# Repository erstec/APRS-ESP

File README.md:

# APRS-ESP32 Project — v2.1

APRS-ESP32 is an APRS AFSK1200 Tracker + Digipeater + Internet Gateway for Espressif ESP32/ESP32-S3 MCUs.

> **v2.0 breaking change:** filesystem migrated from SPIFFS to LittleFS. All web UI assets are stored on LittleFS. A full flash (firmware + filesystem) is required when upgrading from v1.x.

Feel free to ask [Me](https://github.com/erstec) by creating a [Discussion](https://github.com/erstec/APRS-ESP/discussions/new), by e-mail.

---

## Features

### Firmware

- IGate (APRS-IS internet gateway)
- Digipeater
- Tracker with SmartBeaconing
- Fixed position and item beaconing
- APRS message receive: inbox with unread counter, popup notification, and automatic ACK
- Received APRS packet list with raw packet viewer
- OLED display with rotary encoder menu, live GNSS status screen, and graphical APRS symbol picker
- Automatic GNSS configuration on boot: GPS+BeiDou+GLONASS, NMEA output filtered to GGA/GSA/RMC (T-TWR Plus / Quectel L76K)
- Web interface for all configuration
- Interactive map location picker with GPS fix-from-device button; offline tiles bundled for use without internet
- Graphical APRS symbol picker in web UI and OLED menu
- Visual APRS-IS filter builder (range, prefix, buddy, type tokens)
- Battery / PMU status dashboard card (charger state, voltage, %, VBUS, sys voltage, PMU temperature)
- Configuration backup / restore (JSON)
- OTA firmware update via web interface

### Supported Hardware

| Target | Notes |
| ------ | ----- |
| **LilyGO T-TWR Plus (Rev 2.0)** | Fully supported, recommended |
| **LilyGO T-TWR V1** | Supported (UNTESTED) with hardware mods — see [doc/mod-hw-devel.md](doc/mod-hw-devel.md) |
| **ESP32-DevKitC + SA818/SA868** | DIY build — see schematics below |

> **esp32dev-t-twr-mod is removed** — that variant was an intermediate hardware mod that is no longer maintained.

---

## OLED Display

### Main status screen

The display is 128×64 pixels. The speed/heading zone uses a large proportional font; all other zones use the default 6×8 bitmap font. `[sat]` `[clk]` `[->]` represent 8×7 px graphical bitmap icons.

```text
N0CALL-9              A+ [wifi][bat]  <- callsign / APRS-IS / WiFi / battery
                                      | large font zone
  45 km/h                    265°     <- speed (left) · heading (right)
                                      |
N0000.00  W00000.00                   <- coordinates (NMEA)
AA00aa    12:34:56           0m       <- locator / time / altitude
[sat]8++GPS        SB TN IS RI       <- satellites / sync source / flags
[clk]42s   AUTO      [->]1234        <- GPS age / send mode / distance
```

| Zone | Position | Content | Values / meaning |
| ---- | -------- | ------- | ---------------- |
| Callsign | left | **Callsign + SSID** | `{MYCALL}-{SSID}` |
| Callsign | right | **APRS-IS status** | `A+` connected, `A-` disconnected (only when APRS-IS enabled) |
| Callsign | right | **WiFi icon** | Rising signal bars = connected to AP; X + bar = disconnected (only when WiFi enabled) |
| Callsign | right | **Battery icon** | Outline + proportional fill; lightning bolt when charging |
| Speed/Heading | left | **Speed** | Ground speed in km/h (large font); `Waiting for FIX` / `NO GNSS` when no satellites |
| Speed/Heading | right | **Heading** | Course in degrees + ° (large font); hidden when no satellites |
| Coordinates | full | **Lat + Lon** | NMEA format `NDDMM.MM WDDDMM.MM`; zeroed when no fix |
| Locator row | left | **QTH locator** | Maidenhead grid square (6-char); `------` when no GPS fix |
| Locator row | center | **Time** | `HH:MM:SS` local time; `NO TIME` if not yet synced |
| Locator row | right | **Altitude** | Metres above sea level; blank when no fix |
| Satellites | left | **[sat icon] Satellite info** | `{count}{fix}{pkt}` — count; `+`/`-` for valid fix; `+`/`-` for GPS packets received |
| Satellites | left | **Time sync source** | `GPS`, `NTP`, `APR` = source; `NO` = not synced |
| Satellites | right | **Beacon mode + flags** | `SB` SmartBeaconing, `T{n}` = fixed interval (min); `TN` RF, `TM` telemetry, `DG` digi, `IS` APRS-IS, `RI` RF→IGate, `IR` IGate→RF |
| Bottom | left | **[clock icon] GPS age** | Seconds since last valid fix; `--s` when no fix |
| Bottom | center | **Send mode** | `AUTO` (GPS→Fixed fallback), `GPS` (GPS-only), `FIX` (fixed position) |
| Bottom | right | **[arrow icon] Distance** | Distance travelled since last beacon; `0` when no fix |

### Non-tracker screen (IGate / Digipeater / fixed-position mode)

When operating as an IGate, Digipeater, or fixed-position beacon (GPS mode = Fixed), the tracker speed/heading zone is replaced with a station monitor view.

```text
N0CALL-9              A+ [wifi][bat]  <- callsign / APRS-IS / WiFi / battery
                                      | large font zone
           N0CALL-1                   <- last-heard station callsign (centered)
                                      |
           RF 42s ago                 <- source (RF/IS) + age since last heard
RX:1234              DG:56            <- total packets received / digipeated
RI:78                IR:9             <- RF→IGate / IGate→RF counts
[sat]8++NTP                12:34:56  <- satellites / sync source / time
                    SB TN IS RI IR   <- beacon mode + active service flags
```

| Zone | Position | Content | Values / meaning |
| ---- | -------- | ------- | ---------------- |
| Callsign | left | **Callsign + SSID** | `{MYCALL}-{SSID}` |
| Callsign | right | **APRS-IS status** | `A+` connected, `A-` disconnected (only when APRS-IS enabled) |
| Callsign | right | **WiFi icon** | Rising bars = connected; X + bar = disconnected (only when WiFi enabled) |
| Callsign | right | **Battery icon** | Outline + proportional fill; lightning bolt when charging |
| Large zone | center | **Last-heard callsign** | Most recently decoded station (RF or APRS-IS); blank until first packet |
| Large zone | center | **Source + age** | `RF` or `IS` + time since last packet (`Xs ago`, `Xm ago`, `Xh ago`); `---` if none yet |
| Stats | left | **RX count** | Total packets received |
| Stats | right | **DG count** | Total packets digipeated |
| Stats | left | **RI count** | Packets gated RF → APRS-IS |
| Stats | right | **IR count** | Packets injected APRS-IS → RF |
| Satellites | left | **[sat icon] Satellite info** | `{count}{fix}{pkt}` — count; `+`/`-` for valid fix; `+`/`-` for GPS packets received |
| Satellites | left | **Time sync source** | `GPS`, `NTP`, `APR` = source; `NO` = not synced |
| Satellites | right | **Time** | `HH:MM:SS` local time |
| Flags | right | **Beacon mode + flags** | `SB` SmartBeaconing, `T{n}` = fixed interval (min); `TN` RF, `TM` telemetry, `DG` digi, `IS` APRS-IS, `RI` RF→IGate, `IR` IGate→RF |

---

## Rotary Encoder Menu

### Short press — enter main menu

Scroll with the encoder knob. Press to select / toggle each item:

| # | Item | Action |
| - | ---- | ------ |
| 0 | Send Beacon | Transmit position now |
| 1 | Beacon Mode | Select: SmartBeaconing (SB) or fixed interval 1/2/5/10/15/20/30/60 min |
| 2 | WiFi | Cycle: OFF → AP → STA → AP+STA |
| 3 | APRS-IS | Toggle ON/OFF |
| 4 | Digi | Toggle digipeater ON/OFF |
| 5 | RF/TNC | Toggle RF modem ON/OFF |
| 6 | RF Power | Toggle Low / High transmit power |
| 7 | Send Mode | Cycle: AUTO (GPS→Fixed fallback) / GPS only / Fixed position |
| 8 | Callsign-SSID | Edit callsign (A-Z, 0-9, min 3 chars, max 6) then SSID (0-15) |
| 9 | Symbol | Graphical APRS symbol picker: scroll through 12 presets (Car, House, Hiker, Bike, …), OLED shows the symbol bitmap + table/char code |
| 10 | Brightness | Set OLED brightness: Min / Low / Medium / High / Max |
| 11 | Auto-Dim | Set auto-dim timeout and level |
| 12 | Locator Popup | Duration of grid locator popup (OFF or 1–10 s) |
| 13 | APRS RX Popup | Duration of received packet popup (OFF or 1–10 s) |
| 14 | SMS Popup | Duration of incoming APRS message popup (OFF / 15 / 30 / 60 s); OFF falls back to transient RX popup |
| 15 | RX Packet List | Scrollable list of received APRS packets; press to view full raw packet |
| 16 | MSG Inbox | Received APRS messages; shows unread count |
| 17 | GNSS Status | Live GNSS data screen (see below) |
| 18 | Battery Status | Live battery / PMU status (charger state, voltage, %, VBUS, sys voltage, PMU temp) |
| 19 | About | Firmware version, callsign and IP address |
| 20 | Factory Reset | Erase all settings (YES/NO confirmation) |

Long press from inside the menu → exit without saving.

### GNSS Status screen (item 17)

Live GNSS data, updated every second. Press to return to menu.

```text
   GNSS STATUS
GPS:5  BDS:3  GLO:4
Lat: 5412.34N
Lon: 02512.34E
Alt: 123.4m  3D
Spd: 12.3  Crs: 180
HDOP:1.2 Sat:12 #17
press: back
```

| Row | Content |
| --- | ------- |
| 1 | Satellites **in use** per constellation: GPS / BDS (BeiDou) / GLO (GLONASS) |
| 2 | Latitude in NMEA format (DDMM.MMN/S); `--------` when no fix |
| 3 | Longitude in NMEA format (DDDMM.MME/W); `---------` when no fix |
| 4 | Altitude in metres + fix type (`3D` / `2D`); `---` when no fix |
| 5 | Ground speed (km/h) and course (degrees); `0` when no fix |
| 6 | HDOP value, total satellites in use, rolling packet counter (`#XX`) — visible even before a fix to confirm the module is alive and sending |

### Long press — quick action picker

Hold the button. A large message cycles through quick actions every 2 seconds:

| Shown | Action on release |
| ----- | ----------------- |
| **BEACON** | Send position packet |
| **WiFi SW** | Toggle WiFi ON/OFF (device restarts) |
| **RF SW** | Toggle RF modem ON/OFF |
| **SB SW** | Toggle SmartBeaconing ON/OFF |
| **RESET** | Factory reset (device restarts) |
| **Cancel** | Do nothing |

*Release when the desired action is shown.*

---

## BOOT Button (GPIO0, all boards)

The physical BOOT button on the ESP32 module provides the same timed quick actions on boards **without** a rotary encoder:

- Short press (< 5 s) → Send position
- Hold **5 s** → Toggle WiFi (shows "WiFi SW")
- Hold **10 s** → Toggle RF modem (shows "RF SW")
- Hold **15 s** → Toggle SmartBeaconing (shows "SB SW")
- Hold **20 s** → Factory reset (shows "Reset")
- Hold **25 s+** → Cancel

*Release when the desired message appears on screen.*

---

## Side Buttons (T-TWR Plus only)

The T-TWR Plus has three physical buttons in addition to the rotary encoder:

| Button | Short press | Long press (2 s) |
| ------ | ----------- | ---------------- |
| **Lower** | Toggle OLED display on/off; dismiss active popup | Toggle RF power High ↔ Low |
| **Middle** | Show battery status popup (voltage, %, charge state); dismiss active popup | — |
| **Upper** | Send beacon now | Toggle RF/TNC on/off |

> On boards **without** a rotary encoder, SW1/BOOT reverts to the timed BOOT button actions described above.

---

## Flashing Firmware

### First-time flash — new device or upgrade from v1.x

> **v2.0 note:** upgrading from v1.x requires a full flash (firmware + filesystem). The factory `.bin` contains everything — one file, one step.

#### Browser flasher — no software to install (recommended)

Works in **Chrome, Edge or Firefox** on any OS via the Web Serial API.

1. [Download](https://github.com/erstec/APRS-ESP/releases) the factory binary for your hardware, e.g. `firmware-lilygo-t-twr-plus-2.1.factory.bin`
2. Open **<https://espressif.github.io/esptool-js/>** in Chrome, Edge or Firefox
3. Click **Connect** — select the **ESP32-S3 native USB** port (listed as `USB JTAG/serial debug unit`, VID `303a`), not the CH340 UART port
4. Add one row: offset **`0x0`**, select the downloaded `.factory.bin` file
5. Click **Program** — erases flash and writes everything in one pass

#### Via USB script (Python + esptool)

```sh
# Linux / macOS
bin/device-install.sh -f firmware-lilygo-t-twr-plus-2.1.factory.bin

# Windows
bin\device-install.bat -f firmware-lilygo-t-twr-plus-2.1.factory.bin
```

Requires Python 3 and `pip install esptool`. The `-p PORT` flag is optional (esptool auto-detects).

#### From source (PlatformIO)

```bash
pio run -e lilygo-t-twr-plus -t upload
pio run -e lilygo-t-twr-plus -t uploadfs
```

---

## Updating Firmware

### Via web interface (easiest, no USB needed)

> **Before updating:** export your config (Storage tab → Download config). Restore it after flashing via the same tab if needed.

Go to the **Firmware** tab in the web UI:

- Upload `firmware-lilygo-t-twr-plus-2.1-update.bin` → flashes app only, config is preserved
- Upload `littlefs-lilygo-t-twr-plus-2.1.bin` → updates web assets (upload after firmware if web UI changed)

The page auto-detects which file type you selected by filename.

### Via browser flasher (upgrade from v1.x or broken web UI)

Same steps as first-time flash above — use the `.factory.bin` at offset `0x0`.

### Via USB script

```sh
bin/device-update.sh -f firmware-lilygo-t-twr-plus-2.1-update.bin
```

> After any major update: export a configuration backup first — config format changes between versions are not guaranteed.

---

## WiFi / Web Interface

On first boot the device creates a WiFi AP:

- **SSID**: `APRS-ESP32`
- **Password**: `aprs-esp32`
- **URL**: <http://192.168.4.1>

### Web UI tabs

| Tab | Contents |
| --- | -------- |
| **Dashboard** | System status (CPU temp, free heap, uptime, WiFi RSSI); **Battery Status** (charger state, voltage %, VBUS, sys voltage, PMU temp); GNSS status (fix, coords, altitude, speed, sats/HDOP, per-constellation counts); packet statistics; last heard stations; top senders |
| **Config** | APRS callsign, SSID, passcode, beacon interval / SmartBeaconing, digi path, symbol (graphical tile picker + manual table/char fields); **interactive Leaflet map** with draggable marker and "Use current GPS location" button (offline tiles bundled) |
| **Radio** | SA818/SA868: TX/RX frequency, bandwidth, RF power, squelch, volume; OLED brightness and auto-dim timeout |
| **Service** | APRS-IS enable/server/port/filter with **visual filter builder** (range, prefix, buddy, type tokens); TNC / RF→INET / INET→RF / telemetry / digipeater toggles; digi delay; TX time slot; BPF enable |
| **System** | Manual date/time set, NTP sync, timezone offset; WiFi AP and client config with live status (mode, IP, MAC, SSID, gateway, DNS); reboot |
| **Test** | Send beacon now; send raw TNC2 packet; live audio **VU meter**; APRS-IS terminal log |
| **Files** | LittleFS file browser — upload, download, delete; in-browser **CodeMirror editor** for web asset files (HTML, JS, CSS, JSON, config) |
| **Firmware** | OTA firmware update (`-update.bin`) and filesystem update (`littlefs-*.bin`) |
| **Configuration** | Device info (board, firmware version, chip ID); config **backup** (JSON download) and **restore** (JSON upload) |

---

## Serial Monitor (Development Tool)

`tools/monitor.py` is a live desktop monitor for development and field debugging. It reads the device serial port, parses structured JSON log lines, and displays them in real-time cards.

### Requirements

```sh
pip install -r tools/requirements.txt   # dearpygui, pyserial
```

### Usage

```sh
python3 tools/monitor.py
```

The best available ESP32 port is pre-selected on startup. Connect, disconnect, and optionally log to file via the toolbar.

### Cards

| Card | Content |
| ---- | ------- |
| **System** | Time, uptime, free heap, CPU temp, WiFi RSSI, IP address |
| **Config** | Callsign, path, beacon, send mode, RX/TX freq, mode flags, WiFi mode, routing, APRS-IS |
| **Battery** | Charge %, voltage, VBUS, system voltage, charger state, PMU temp |
| **GPS** | Fix, lat/lon, altitude, speed, heading, HDOP, sats (GPS/BDS/GLO), data age |
| **APRS** | Packet counters (all/drop/RF→IS/IS→RF) |
| **SmartBeaconing** | Distance, speed, elapsed, rate, turn angle, will-TX flag |
| **RF** | PTT state, last TX packet, last RX packet, last SMS addressed to this station |
| **Log** | Colour-coded raw serial log (STATUS / DEBUG / SB / TX / BTN / MSG / PKT); toggleable file logging |

---

## Building from Source

Requirements: PlatformIO + VS Code

```bash
# Clone and build
git clone https://github.com/erstec/APRS-ESP
cd APRS-ESP
pio run -e lilygo-t-twr-plus             # build
pio run -e lilygo-t-twr-plus -t upload   # flash firmware
pio run -e lilygo-t-twr-plus -t uploadfs # flash filesystem (safe — config is in NVS)
```

Available environments: `lilygo-t-twr-plus`, `lilygo-t-twr-v1`, `esp32dev-sa818-868`

### Configuration storage

Configuration is stored in **ESP32 NVS** (Non-Volatile Storage), a dedicated flash partition separate from both the firmware and the LittleFS filesystem. This means:

- Flashing new firmware does **not** erase config
- Flashing the filesystem (`uploadfs`) does **not** erase config
- Adding new config fields in future firmware versions requires no migration code — missing NVS keys return their built-in defaults automatically
- Config backup/restore via the web UI uses JSON (download/upload on the Storage tab)

To reset to factory defaults: hold the BOOT button during power-on, or use Menu / Quick Menu.

---

## Hardware (DIY build)

- ESP32-DevKitC-v4 (or pin-compatible)
- SA818 / SA868 RF modem
- NMEA serial GNSS receiver
- SSD1306 0.96" or SH1106 1.3" OLED
- Rotary encoder (optional)

**Schematics:** [PDF](hardware/APRS-ESP32_SA8x8_Rev_D_Schematics.pdf)

**PCB layout:** [PDF](hardware/APRS-ESP32_SA8x8_Rev_D_PCB.pdf)

**Gerbers:** [ZIP](hardware/GERBER/APRS-ESP32_SA8x8_V1.7_Rev_D_2022-10-27.zip)

**BOM:** [TXT](hardware/APRS-ESP32_SA8x8_Rev_D_BOM.txt)

---

## Credits

Code from:

- <https://github.com/nakhonthai/ESP32IGate>
- <https://github.com/sh123/aprs_tracker>
- <https://github.com/meshtastic/firmware> — build system and CI

Hardware inspired by:

- <https://github.com/nakhonthai/ESP32IGate>
- <https://github.com/handiko/Dorji-TX-Shield>

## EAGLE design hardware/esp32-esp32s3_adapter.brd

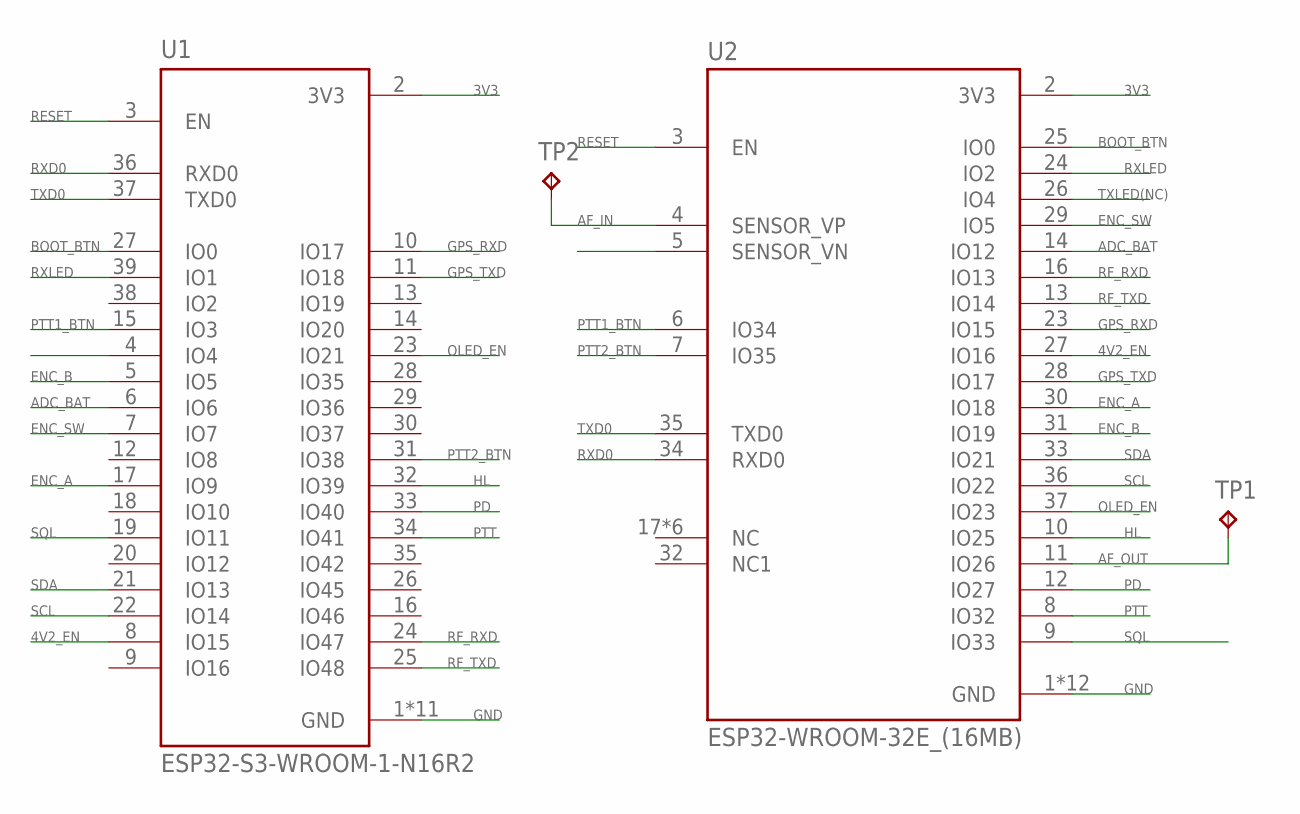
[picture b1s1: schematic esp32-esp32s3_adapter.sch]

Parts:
TP1, TP2: TPB1,27; B1,27
U1: ESP32-S3-WROOM-1-N16R2; XCVR_ESP32-S3-WROOM-1-N16R2
U2: ESP32-WROOM-32E_(16MB); XCVR_ESP32-WROOM-32E_(16MB)

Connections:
3V3: U1.2 (3V3), U2.2 (3V3)
4V2_EN: U1.8 (IO15), U2.27 (IO16)
ADC_BAT: U1.6 (IO6), U2.14 (IO12)
AF_IN: TP2.TP, U2.4 (SENSOR_VP)
AF_OUT: TP1.TP, U2.11 (IO26)
BOOT_BTN: U1.27 (IO0), U2.25 (IO0)
ENC_A: U1.17 (IO9), U2.30 (IO18)
ENC_B: U1.5 (IO5), U2.31 (IO19)
ENC_SW: U1.7 (IO7), U2.29 (IO5)
GND: U1.1 (GND), U1.40 (GND), U1.41_1 (GND), U1.41_2 (GND), U1.41_3 (GND), U1.41_4 (GND), U1.41_5 (GND), U1.41_6 (GND), U1.41_7 (GND), U1.41_8 (GND), U1.41_9 (GND), U2.1 (GND), U2.15 (GND), U2.38 (GND), U2.39_1 (GND), U2.39_2 (GND), U2.39_3 (GND), U2.39_4 (GND), U2.39_5 (GND), U2.39_6 (GND), U2.39_7 (GND), U2.39_8 (GND), U2.39_9 (GND)
GPS_RXD: U1.10 (IO17), U2.23 (IO15)
GPS_TXD: U1.11 (IO18), U2.28 (IO17)
HL: U1.32 (IO39), U2.10 (IO25)
OLED_EN: U1.23 (IO21), U2.37 (IO23)
PD: U1.33 (IO40), U2.12 (IO27)
PTT: U1.34 (IO41), U2.8 (IO32)
PTT1_BTN: U1.15 (IO3), U2.6 (IO34)
PTT2_BTN: U1.31 (IO38), U2.7 (IO35)
RESET: U1.3 (EN), U2.3 (EN)
RF_RXD: U1.24 (IO47), U2.16 (IO13)
RF_TXD: U1.25 (IO48), U2.13 (IO14)
RXD0: U1.36 (RXD0), U2.34 (RXD0)
RXLED: U1.39 (IO1), U2.24 (IO2)
SCL: U1.22 (IO14), U2.36 (IO22)
SDA: U1.21 (IO13), U2.33 (IO21)
SQL: U1.19 (IO11), U2.9 (IO33)
TXD0: U1.37 (TXD0), U2.35 (TXD0)
TXLED(NC): U2.26 (IO4)

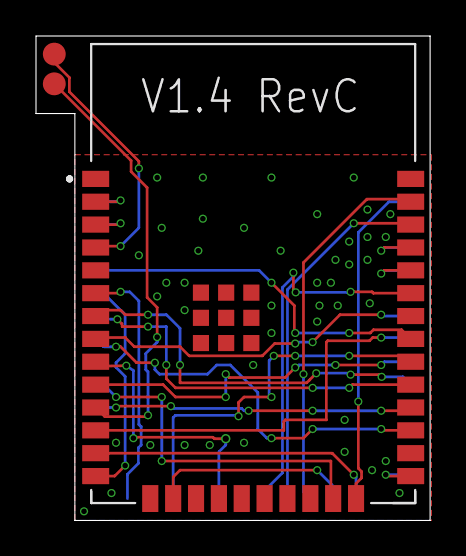
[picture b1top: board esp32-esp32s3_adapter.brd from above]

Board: 2 copper layers, 21.9 x 26.9 mm, 4 parts (0 on the bottom side), 27 nets.

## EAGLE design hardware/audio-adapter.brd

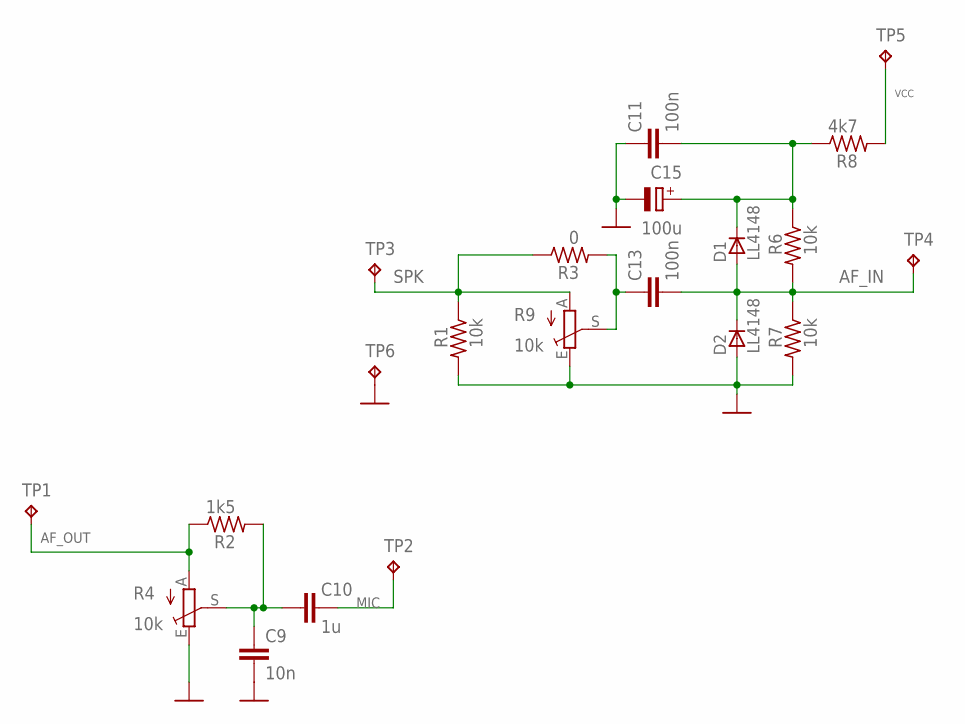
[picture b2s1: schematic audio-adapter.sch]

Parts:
C9: 10n; C0805
C10: 1u; C0805
C11, C13: 100n; C0805
C15: 100u; SMC_D
D1, D2: LL4148; SOD80_DO213AA_MINIMELF
R1, R6, R7: 10k; R0805
R2: 1k5; R0805
R3: 0; R0805
R4, R9: 10k; CA6H
R8: 4k7; R0805
TP1, TP2, TP3, TP4, TP5, TP6: TPB1,27; B1,27

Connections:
AF_IN: C13.2, D1.A, D2.C, R6.2, R7.1, TP4.TP
AF_OUT: R2.1, R4.A, TP1.TP
GND: C9.2, C11.1, C15.-, D2.A, R1.2, R4.E, R7.2, R9.E, TP6.TP
MIC: C10.2, TP2.TP
unnamed: C11.2, C15.+, D1.C, R6.1, R8.1
unnamed: C13.1, R3.2, R9.S
unnamed: C9.1, C10.1, R2.2, R4.S
SPK: R1.1, R3.1, R9.A, TP3.TP
VCC: R8.2, TP5.TP

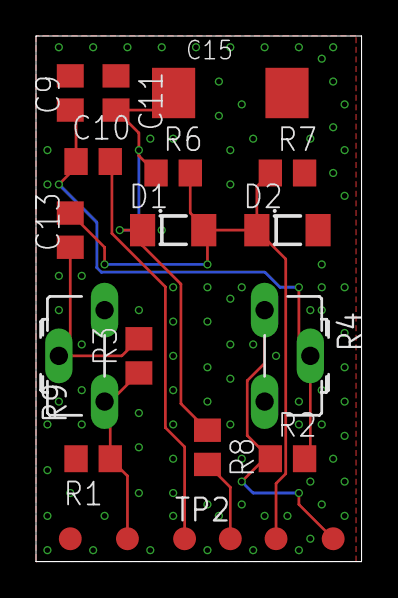
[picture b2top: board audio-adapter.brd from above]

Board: 2 copper layers, 18.1 x 29.2 mm, 21 parts (0 on the bottom side), 9 nets.

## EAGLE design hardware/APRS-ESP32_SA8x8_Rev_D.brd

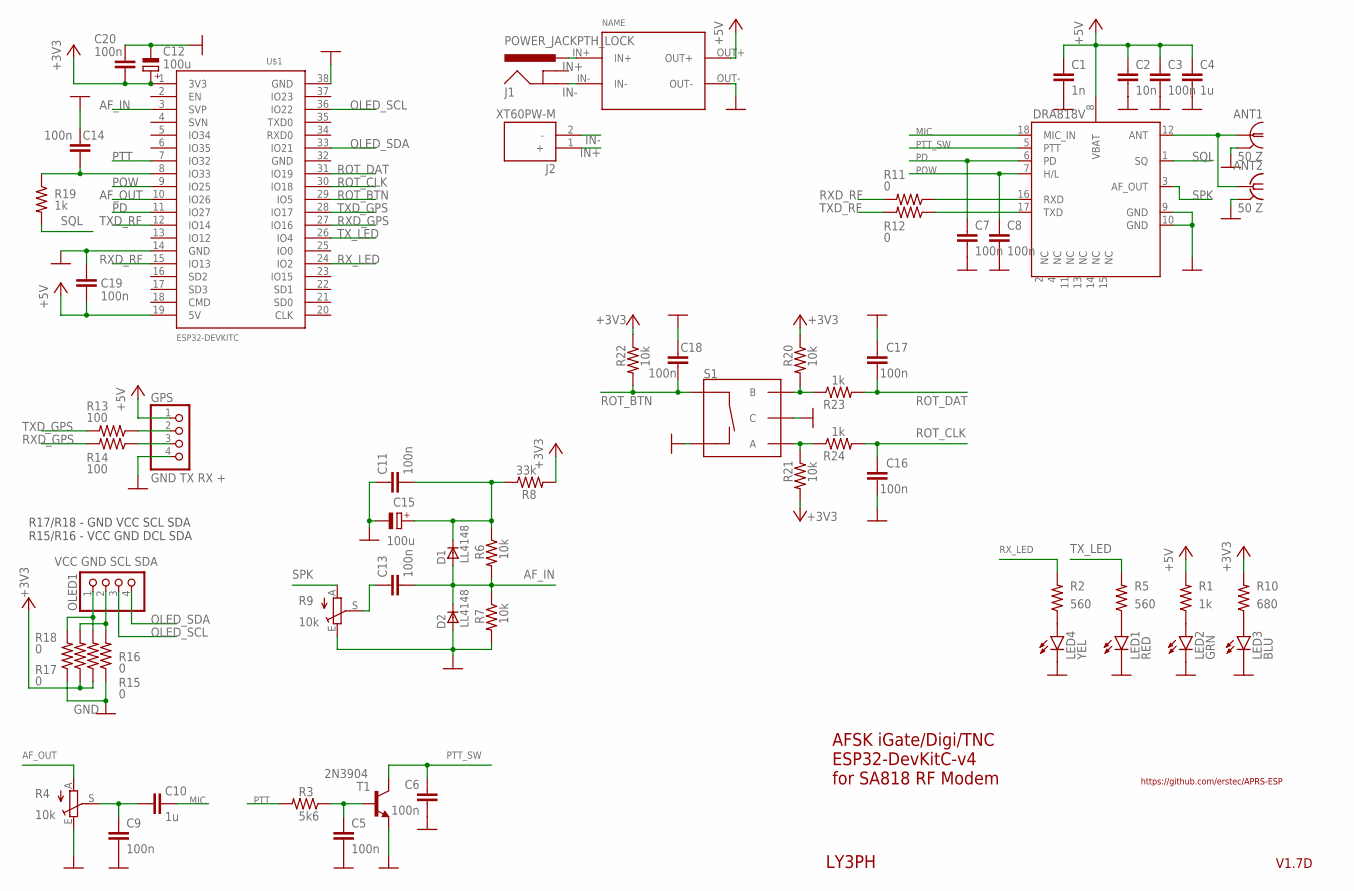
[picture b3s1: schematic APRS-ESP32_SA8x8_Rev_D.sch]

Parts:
ANT1: 50 Z; LTI-SASF54GT
ANT2: 50 Z; J502-ND-142-0701-801/806
C1: 1n; C0805
C2: 10n; C0805
C3, C5, C6, C7, C8, C9, C11, C13, C14, C16, C17, C18, C19, C20: 100n; C0805
C4, C10: 1u; C0805
C12, C15: 100u; SMC_D
D1, D2: LL4148; SOD80_DO213AA_MINIMELF
DRA818V: DRA818A
GPS: GND TX RX +; 1X04
J1: POWER_JACKPTH_LOCK; POWER_JACK_PTH_LOCK
J2: XT60PW-M; AMASS_XT60PW-M
LED1: RED; CHIP-LED0805
LED2: GRN; CHIP-LED0805
LED3: BLU; CHIP-LED0805
LED4: YEL; CHIP-LED0805
OLED1: VCC GND SCL SDA; 1X04
R1, R19, R23, R24: 1k; R0805
R2, R5: 560; R0805
R3: 5k6; R0805
R4, R9: 10k; CA6H
R6, R7, R20, R21, R22: 10k; R0805
R8: 33k; R0805
R10: 680; R0805
R11, R12, R15, R16, R17, R18: 0; R0805
R13, R14: 100; R0805
S1: ENCODER-SWITCH; ROTARY_ENC_PLAIN
T1: 2N3904; SOT23-BEC
U$1: ESP32DEVKITC; ESP32-DEVKITC
U$2: CP8-ADJ

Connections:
+3V3: C12.+, C20.2, R8.2, R10.2, R15.1, R17.1, R20.1, R21.2, R22.1, U$1.1 (3V3)
+5V: C1.1, C2.1, C3.1, C4.1, C19.2, DRA818V.8 (VBAT), GPS.1, R1.2, U$1.19 (5V), U$2.OUT+
AF_IN: C13.2, D1.A, D2.C, R6.2, R7.1, U$1.3 (SVP)
AF_OUT: R4.A, U$1.10 (IO26)
GND: ANT1.2, ANT1.3 (2), ANT1.4 (2), ANT1.5 (2), ANT2.G@1 (2), ANT2.G@2 (2), ANT2.G@3 (2), ANT2.G@4 (2), C1.2, C2.2, C3.2, C4.2, C5.2, C6.2, C7.2, C8.2, C9.2, C11.1, C12.-, C14.2, C15.-, C16.2, C17.1, C18.1, C19.1, C20.1, D2.A, DRA818V.9 (GND), DRA818V.10 (GND), GPS.4, LED1.C, LED2.C, LED3.C, LED4.C, R4.E, R7.2, R9.E, R16.1, R18.1, S1.C, S1.SW-, T1.E, U$1.14 (GND), U$1.38 (GND), U$2.OUT-
IN+: J1.PWR, J2.1 (+), U$2.IN+
IN-: J1.GND, J2.2 (-), U$2.IN-
MIC: C10.2, DRA818V.18 (MIC_IN)
unnamed: LED1.A, R5.1
unnamed: C11.2, C15.+, D1.C, R6.1, R8.1
unnamed: GPS.2, R13.1
unnamed: C13.1, R9.S
unnamed: ANT1.1, ANT2.1, DRA818V.12 (ANT)
unnamed: C5.1, R3.1, T1.B
unnamed: LED4.A, R2.1
unnamed: C9.1, C10.1, R4.S
unnamed: LED3.A, R10.1
unnamed: GPS.3, R14.1
unnamed: DRA818V.16 (RXD), R11.1
unnamed: DRA818V.17 (TXD), R12.1
unnamed: OLED1.2, R16.2, R17.2
unnamed: OLED1.1, R15.2, R18.2
unnamed: C14.1, R19.1, U$1.8 (IO33)
unnamed: LED2.A, R1.1
OLED_SCL: OLED1.3, U$1.36 (IO22)
OLED_SDA: OLED1.4, U$1.33 (IO21)
PD: C7.1, DRA818V.6 (PD), U$1.11 (IO27)
POW: C8.1, DRA818V.7 (H/L), U$1.9 (IO25)
PTT: R3.2, U$1.7 (IO32)
PTT_SW: C6.1, DRA818V.5 (PTT), T1.C
ROT_BTN: C18.2, R22.2, S1.SW+, U$1.29 (IO5)
ROT_CLK: C16.1, R24.2, U$1.30 (IO18)
ROT_CLK_ROUTE: R21.1, R24.1, S1.A
ROT_DAT: C17.2, R23.2, U$1.31 (IO19)
ROT_DAT_ROUTE: R20.2, R23.1, S1.B
RXD_GPS: R14.2, U$1.27 (IO16)
RXD_RF: R11.2, U$1.15 (IO13)
RX_LED: R2.2, U$1.24 (IO2)
SPK: DRA818V.3 (AF_OUT), R9.A
SQL: DRA818V.1 (SQ), R19.2
TXD_GPS: R13.2, U$1.28 (IO17)
TXD_RF: R12.2, U$1.12 (IO14)
TX_LED: R5.2, U$1.26 (IO4)

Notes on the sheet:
R17/R18 - GND VCC SCL SDA R15/R16 - VCC GND DCL SDA
LY3PH
AFSK iGate/Digi/TNC ESP32-DevKitC-v4 for SA818 RF Modem
V1.7D
https://github.com/erstec/APRS-ESP

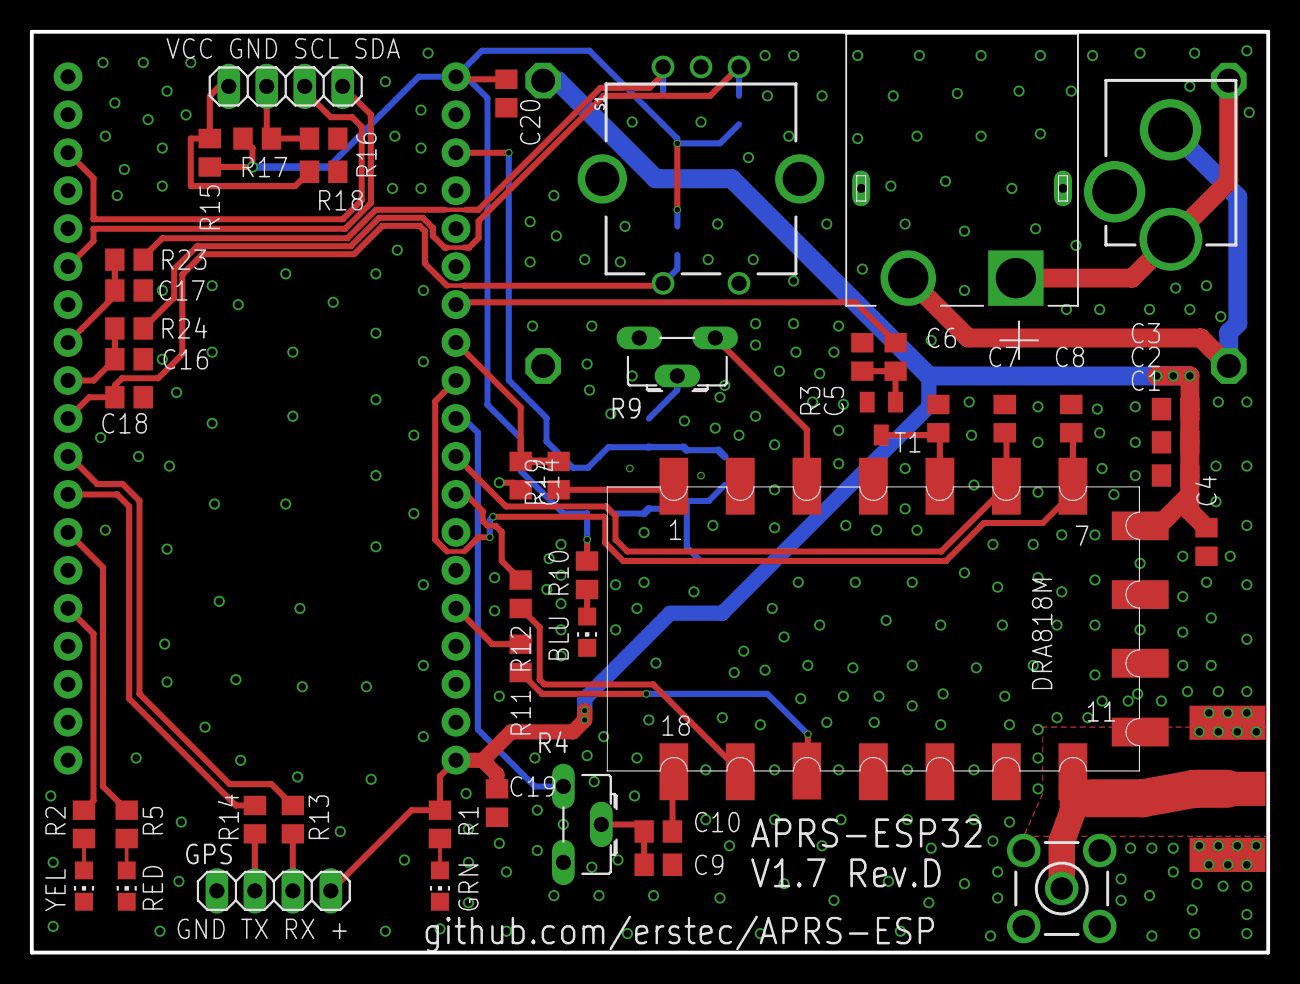
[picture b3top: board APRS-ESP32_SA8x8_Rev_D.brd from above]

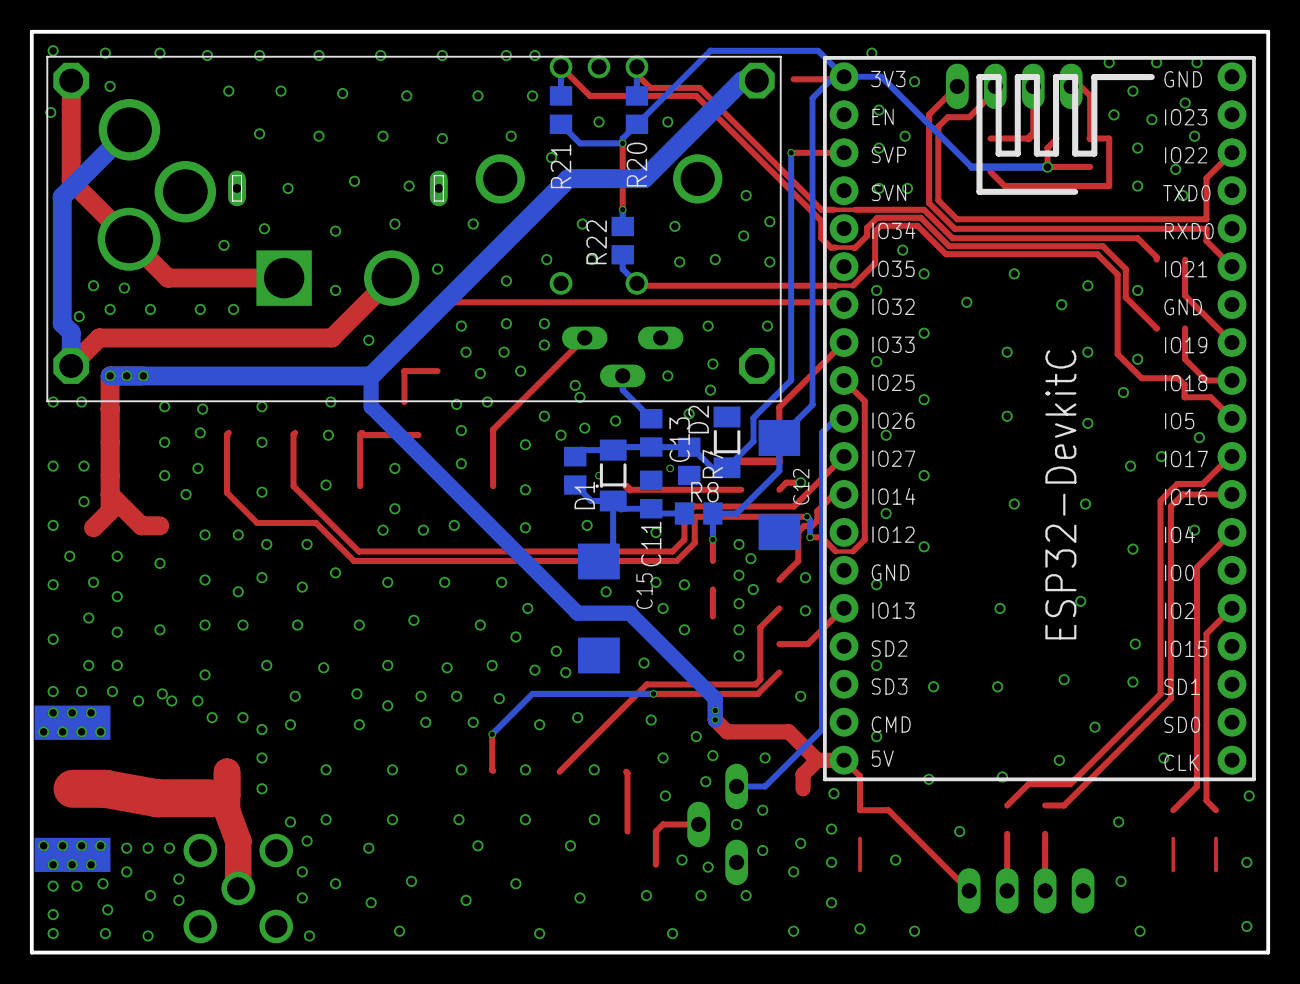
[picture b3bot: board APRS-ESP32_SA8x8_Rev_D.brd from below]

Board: 2 copper layers, 82.7 x 61.6 mm, 61 parts (14 on the bottom side), 43 nets.

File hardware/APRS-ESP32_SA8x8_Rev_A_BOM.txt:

Qty Value              Device                    Package                  Parts                       Description                                           MF                 MPN          OC_FARNELL OC_NEWARK POPULARITY PROD_ID    SF_ID     SF_SKU    SPICEPREFIX
4   0                  R-US_R0805                R0805                    R15, R16, R17, R18          RESISTOR, American symbol                                                                                                                                       
4   100                R-US_R0805                R0805                    R11, R12, R13, R14          RESISTOR, American symbol                                                                                                                                       
3   560                R-US_R0805                R0805                    R2, R5, R10                 RESISTOR, American symbol                                                                                                                                       
2   1k                 R-US_R0805                R0805                    R1, R19                     RESISTOR, American symbol                                                                                                                                       
1   5k6                R-US_R0805                R0805                    R3                          RESISTOR, American symbol                                                                                                                                       
2   10k                R-US_R0805                R0805                    R6, R7                      RESISTOR, American symbol                                                                                                                                       
1   33k                R-US_R0805                R0805                    R8                          RESISTOR, American symbol                                                                                                                                       

2   10k                TRIM_EU-CA6H              CA6H                     R4, R9                      POTENTIOMETER                                                                                              0                                                    

1   1n                 C-EUC0805                 C0805                    C1                          CAPACITOR, European symbol                                                                                                                                      
1   10n                C-EUC0805                 C0805                    C2                          CAPACITOR, European symbol                                                                                                                                      
9   100n               C-EUC0805                 C0805                    C3, C5, C6, C7, C8, C9, C14 CAPACITOR, European symbol                                                                                                                                      
                                                                          C11, C13
2   1u                 C-EUC0805                 C0805                    C4, C10                     CAPACITOR, European symbol                                                                                                                                      
2   100u               CPOL-EUSMCD               SMC_D                    C12, C15                    POLARIZED CAPACITOR, European symbol                                                                       0                                         C          

1   BLU                LEDCHIP-LED0805           CHIP-LED0805             LED3                        LED                                                                                                        68                                                   
1   GRN                LEDCHIP-LED0805           CHIP-LED0805             LED2                        LED                                                                                                        68                                                   
1   RED                LEDCHIP-LED0805           CHIP-LED0805             LED1                        LED                                                                                                        68                                                   
1   YEL                LEDCHIP-LED0805           CHIP-LED0805             LED4                        LED                                                                                                        68                                                   

2   LL4148             LL4148                    SOD80_DO213AA_MINIMELF   D1, D2                      1N4148 General Purpose Rectifie                                                                                                                                 

1   2N3904             MMBT3904LT1-NPN-SOT23-BEC SOT23-BEC                T1                          NPN Transistror                                                                                            0                                                    

1   ENCODER-SWITCH     ENCODER-SWITCH            ROTARY_ENC_PLAIN         S1                          Rotary Encoder w/ Select Switch                                                                                                            COM-09117            

1   + TX RX GND        PINHD-1X4                 1X04                     GPS                         PIN HEADER                                                                                                 91                                                   
1   VCC GND SCL SDA    PINHD-1X4                 1X04                     OLED1                       PIN HEADER                                                                                                 91                                                   

1   50 Z               LTI-SASF54GT              LTI-SASF54GT             ANT1                        SMA vertical PCB thrue hole jack                                                      unknown    unknown   3                                                    
1   50 Z               SMA-142-0701-801/806      J502-ND-142-0701-801/806 ANT2                        SMA 50 Ohm End Launch Jack Receptacle - Round Contact JOHNSON COMPONENTS 142-0701-801 1608592    90F2624   5                                                    

1   POWER_JACKPTH_LOCK POWER_JACKPTH_LOCK        POWER_JACK_PTH_LOCK      J1                          Power Jack Connector                                                                                                  CONN-08197 PRT-00119                      

1                      DRA818A                   DRA818A                  DRA818V                                                                                                                                                                                     
1   CP8-ADJ            CP8-ADJ                   CP8-ADJ                  U$2                         Voltage regulator                                                                                                                                               
1   ESP32DEVKITC       ESP32DEVKITC              ESP32-DEVKITC            U$1

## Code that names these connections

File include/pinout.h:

/*
    Description:    This file is part of the APRS-ESP project.
                    This file contains the code for pinouts / settings and etc.
    Author:         Ernest / LY3PH
    License:        GNU General Public License v3.0
    Includes code from:
                    https://github.com/nakhonthai/ESP32IGate
*/

#define BOOT_PIN            0

#if defined(BOARD_ESP32DR)

#define BOARD_NAME          "SA818/868"

// SA8x8 radio module
//#define VBAT_PIN            35
//#define POWER_PIN           12
//#define POWER_PIN           23
#define POWER_PIN           25
#define POWERDOWN_PIN       27
#define SQL_PIN             -1

// Interface to the radio / radio module
#define SPK_PIN             ADC1_CHANNEL_0  // Read ADC1_0 From PIN 36(VP)
#define MIC_PIN             26              // Out wave to PIN 26
//#define PTT_PIN             25
#define PTT_PIN             32
#define RX_LED_PIN          2
#define TX_LED_PIN          4
// #define RSSI_PIN            33

// DEBUG UART
#define SERIAL_DEBUG_BAUD   115200

// RF UART
#define SERIAL_RF_UART      1
#define SERIAL_RF_BAUD      9600
#define SERIAL_RF_RXPIN     14
#define SERIAL_RF_TXPIN     13

// GPS UART
#define SERIAL_GPS_UART     2
#define SERIAL_GPS_BAUD     9600
#define SERIAL_GPS_RXPIN    16
#define SERIAL_GPS_TXPIN    17

// I2C OLED
#define OLED_WIDTH          128
#define OLED_HEIGHT         64
#define OLED_SDA_PIN        21
#define OLED_SCL_PIN        22
#define OLED_RST_PIN        -1

// ROTARY ENCODER
#define PIN_ROT_CLK         18
#define PIN_ROT_DT          19
#define PIN_ROT_BTN         5   // IO0 may be handled too?

#endif /* BOARD_ESP32DR */


#if defined(BOARD_TTWR_PLUS)

#define BOARD_NAME          "T-TWR-PLUS"

// SA8x8 radio module
// #define VBAT_PIN            36
#define POWER_PIN           38
#define POWERDOWN_PIN       40
#define SQL_PIN             -1

// Interface to the radio / radio module
#define SPK_PIN             1
#define MIC_PIN             18
#define PTT_PIN             41
#define INVERT_PTT
#define RX_LED_PIN          -1
#define TX_LED_PIN          -1
// #define RSSI_PIN            42

#define MIC_CH_SEL          17

#define PIXELS_PIN          42

#define PMU_IRQ             4

#define USER_BUTTON         3

// DEBUG UART
#define SERIAL_DEBUG_BAUD   115200

// RF UART
#define SERIAL_RF_UART      1
#define SERIAL_RF_BAUD      9600
#define SERIAL_RF_RXPIN     48
#define SERIAL_RF_TXPIN     39

// GPS UART
#define SERIAL_GPS_UART     2
#define SERIAL_GPS_BAUD     9600
#define SERIAL_GPS_RXPIN    5
#define SERIAL_GPS_TXPIN    6

// I2C OLED
#define OLED_WIDTH          128
#define OLED_HEIGHT         64
#define OLED_SDA_PIN        8
#define OLED_SCL_PIN        9
#define OLED_RST_PIN        -1 // POWER ENABLE

// ROTARY ENCODER
#define PIN_ROT_CLK         47
#define PIN_ROT_DT          46
#define PIN_ROT_BTN         21

#endif /* BOARD_TTWR_PLUS */

#if defined(BOARD_TTWR_V1)

#define BOARD_NAME          "T-TWR-V1"

// SA8x8 radio module
// #define VBAT_PIN            36
#define POWER_PIN           39
#define POWERDOWN_PIN       40
#define SQL_PIN             -1

// Interface to the radio / radio module
// #define SPK_PIN             1
#define SPK_PIN             2
#define MIC_PIN             18
#define PTT_PIN             41
#define INVERT_PTT
// #define RX_LED_PIN          -1
// #define TX_LED_PIN          -1
#define RX_LED_PIN          1
#define TX_LED_PIN          1
#define INVERT_LEDS
// #define RSSI_PIN            42

#define MIC_CH_SEL          -1

// #define PIXELS_PIN          42

// #define PMU_IRQ             4

// ADC
// #define ADC_BATTERY         6
// #define BATT_OFFSET         (2) // mV

// DEBUG UART
#define SERIAL_DEBUG_BAUD   115200

// RF UART
#define SERIAL_RF_UART      1
#define SERIAL_RF_BAUD      9600
#define SERIAL_RF_RXPIN     48
#define SERIAL_RF_TXPIN     47

// GPS UART
#define SERIAL_GPS_UART     2
#define SERIAL_GPS_BAUD     9600
#define SERIAL_GPS_RXPIN    17
#define SERIAL_GPS_TXPIN    16

// I2C OLED
#define OLED_WIDTH          128
#define OLED_HEIGHT         64
#define OLED_SDA_PIN        13
#define OLED_SCL_PIN        14
#define OLED_RST_PIN        -1 // POWER ENABLE

// ROTARY ENCODER
#define PIN_ROT_CLK         9
#define PIN_ROT_DT          5
#define PIN_ROT_BTN         7

#endif /* BOARD_TTWR_V1 */

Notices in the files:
parts and their libraries:
SparkFun-Connectors: Licensing: Creative Commons ShareAlike 4.0 International - https://creativecommons.org/licenses/by-sa/4.0
